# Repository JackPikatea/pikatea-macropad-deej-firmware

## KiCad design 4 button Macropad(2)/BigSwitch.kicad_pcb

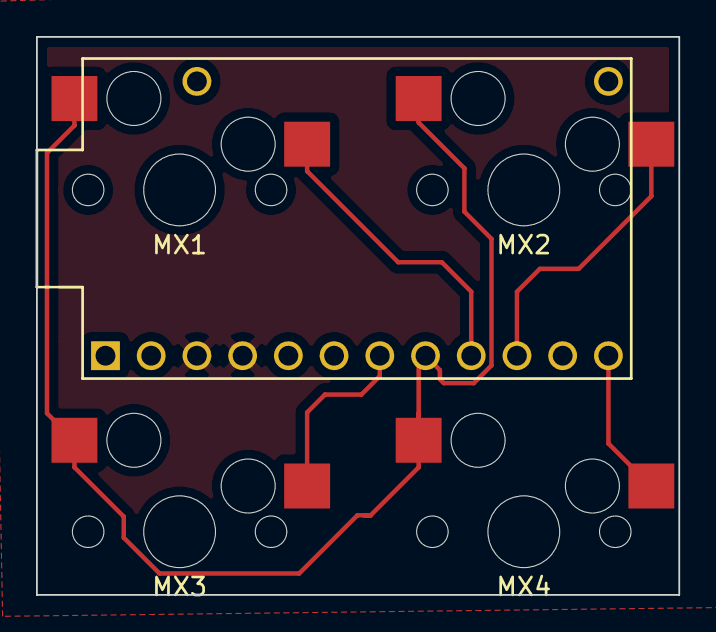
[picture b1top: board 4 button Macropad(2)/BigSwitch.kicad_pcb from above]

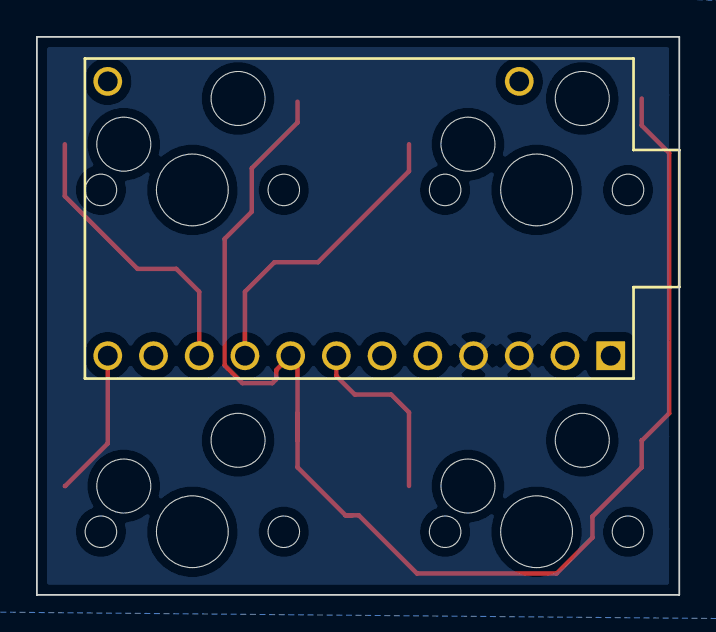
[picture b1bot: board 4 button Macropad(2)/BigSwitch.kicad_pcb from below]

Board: 2 copper layers, 35.7 x 31.0 mm, 5 parts (4 on the bottom side), 6 nets.

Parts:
MX1, MX2, MX3, MX4: MX-NoLED; MXOnly-1U-Hotswap
U1: ProMicro

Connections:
/D4: MX3.1, U1.7
/D5: MX1.2, MX2.2, MX3.2, MX4.2, U1.8
/D6: MX1.1, U1.9
/D7: MX2.1, U1.10
/D9: MX4.1, U1.12
GND: U1.3, U1.4

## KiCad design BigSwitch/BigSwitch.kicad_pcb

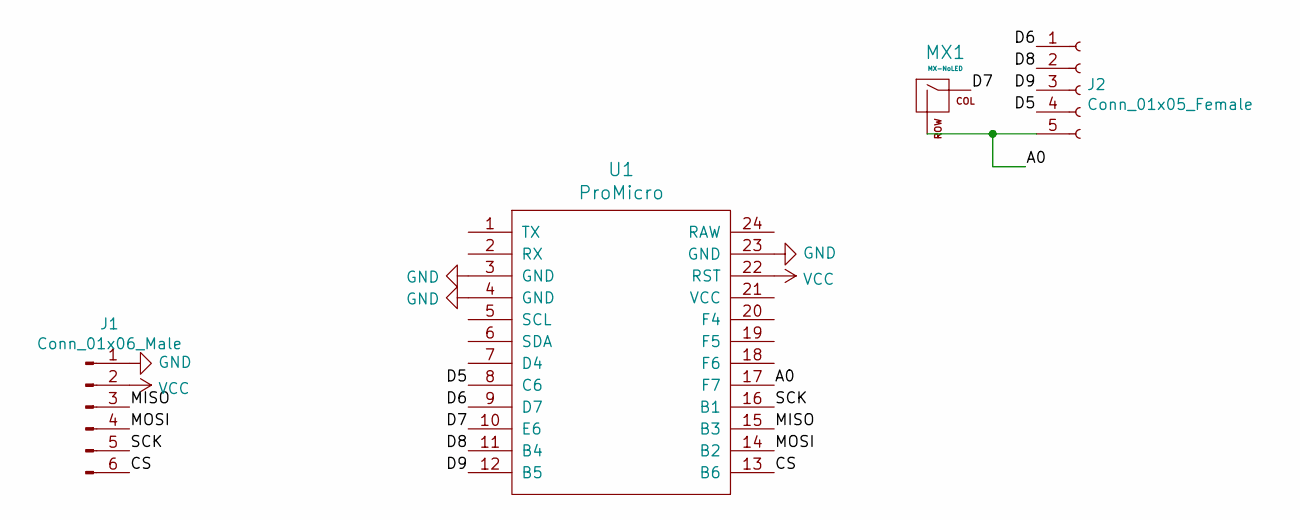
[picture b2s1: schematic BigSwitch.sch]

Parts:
J1: Conn_01x06_Male; SDcardModule-BottomSideDown
J2: Conn_01x05_Female; PinHeader_1x05_P2.54mm_Vertical
MX1: MX-NoLED; BigSwitch
U1: ProMicro

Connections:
/A0: J2.5, MX1.2 (ROW), U1.17 (F7)
/CS: J1.6, U1.13 (B6)
/D5: J2.4, U1.8 (C6)
/D6: J2.1, U1.9 (D7)
/D7: MX1.1 (COL), U1.10 (E6)
/D8: J2.2, U1.11 (B4)
/D9: J2.3, U1.12 (B5)
/MISO: J1.3, U1.15 (B3)
/MOSI: J1.4, U1.14 (B2)
/SCK: J1.5, U1.16 (B1)
GND: J1.1, U1.3 (GND), U1.4 (GND), U1.23 (GND)
VCC: J1.2, U1.22 (RST)

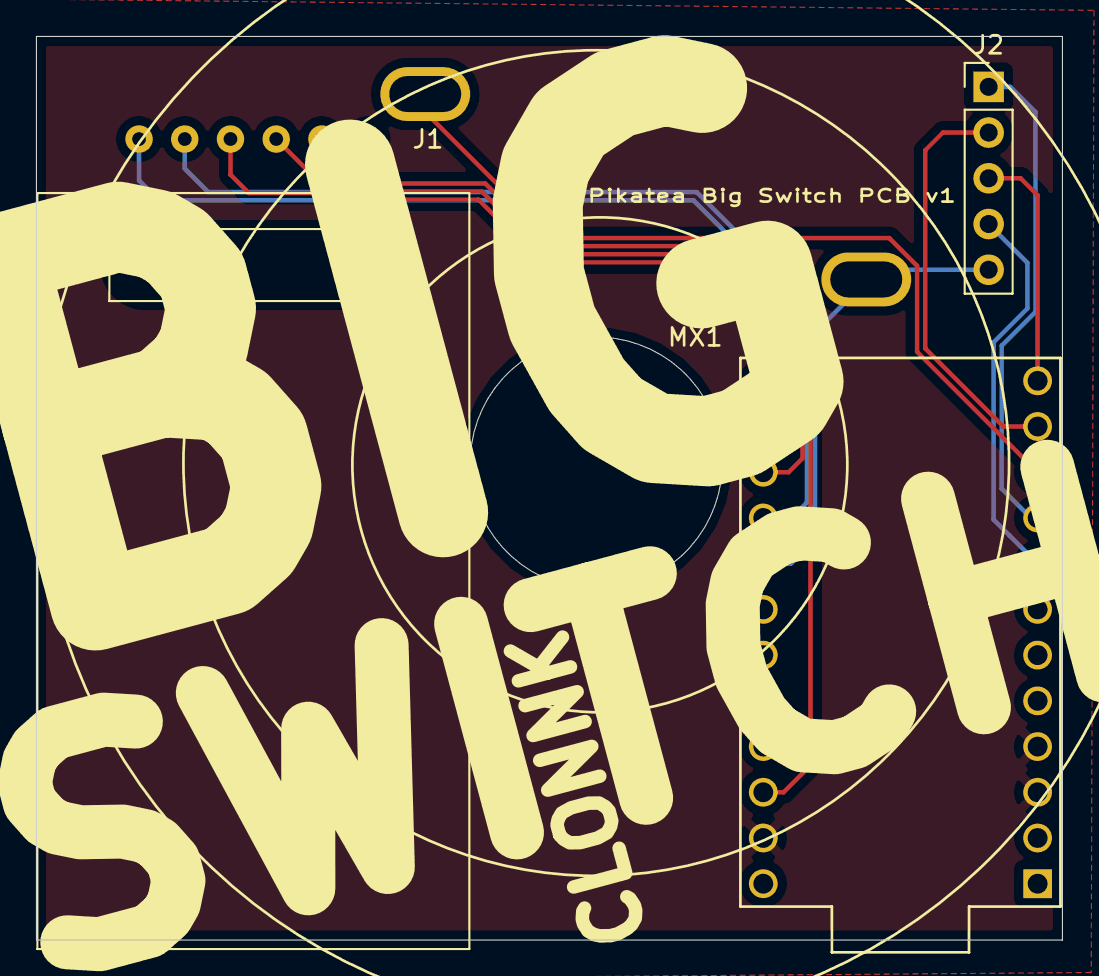
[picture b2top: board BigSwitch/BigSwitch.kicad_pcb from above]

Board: 2 copper layers, 57.0 x 50.2 mm, 4 parts (0 on the bottom side), 12 nets.

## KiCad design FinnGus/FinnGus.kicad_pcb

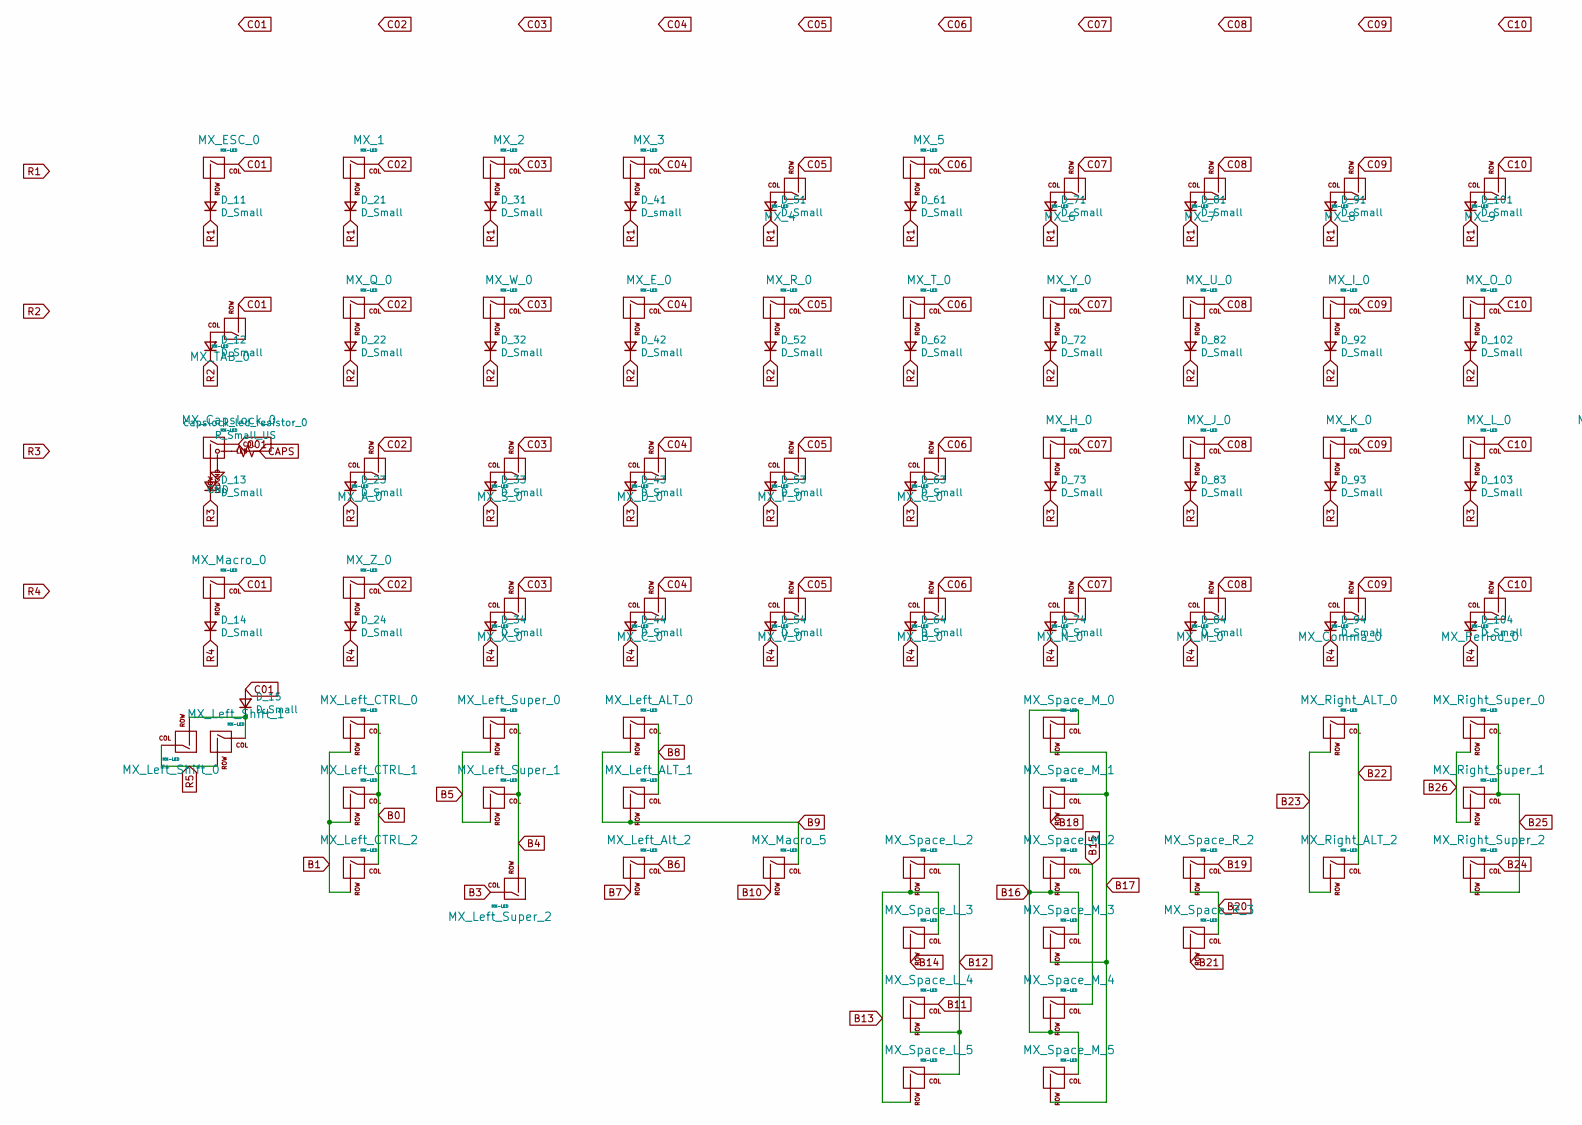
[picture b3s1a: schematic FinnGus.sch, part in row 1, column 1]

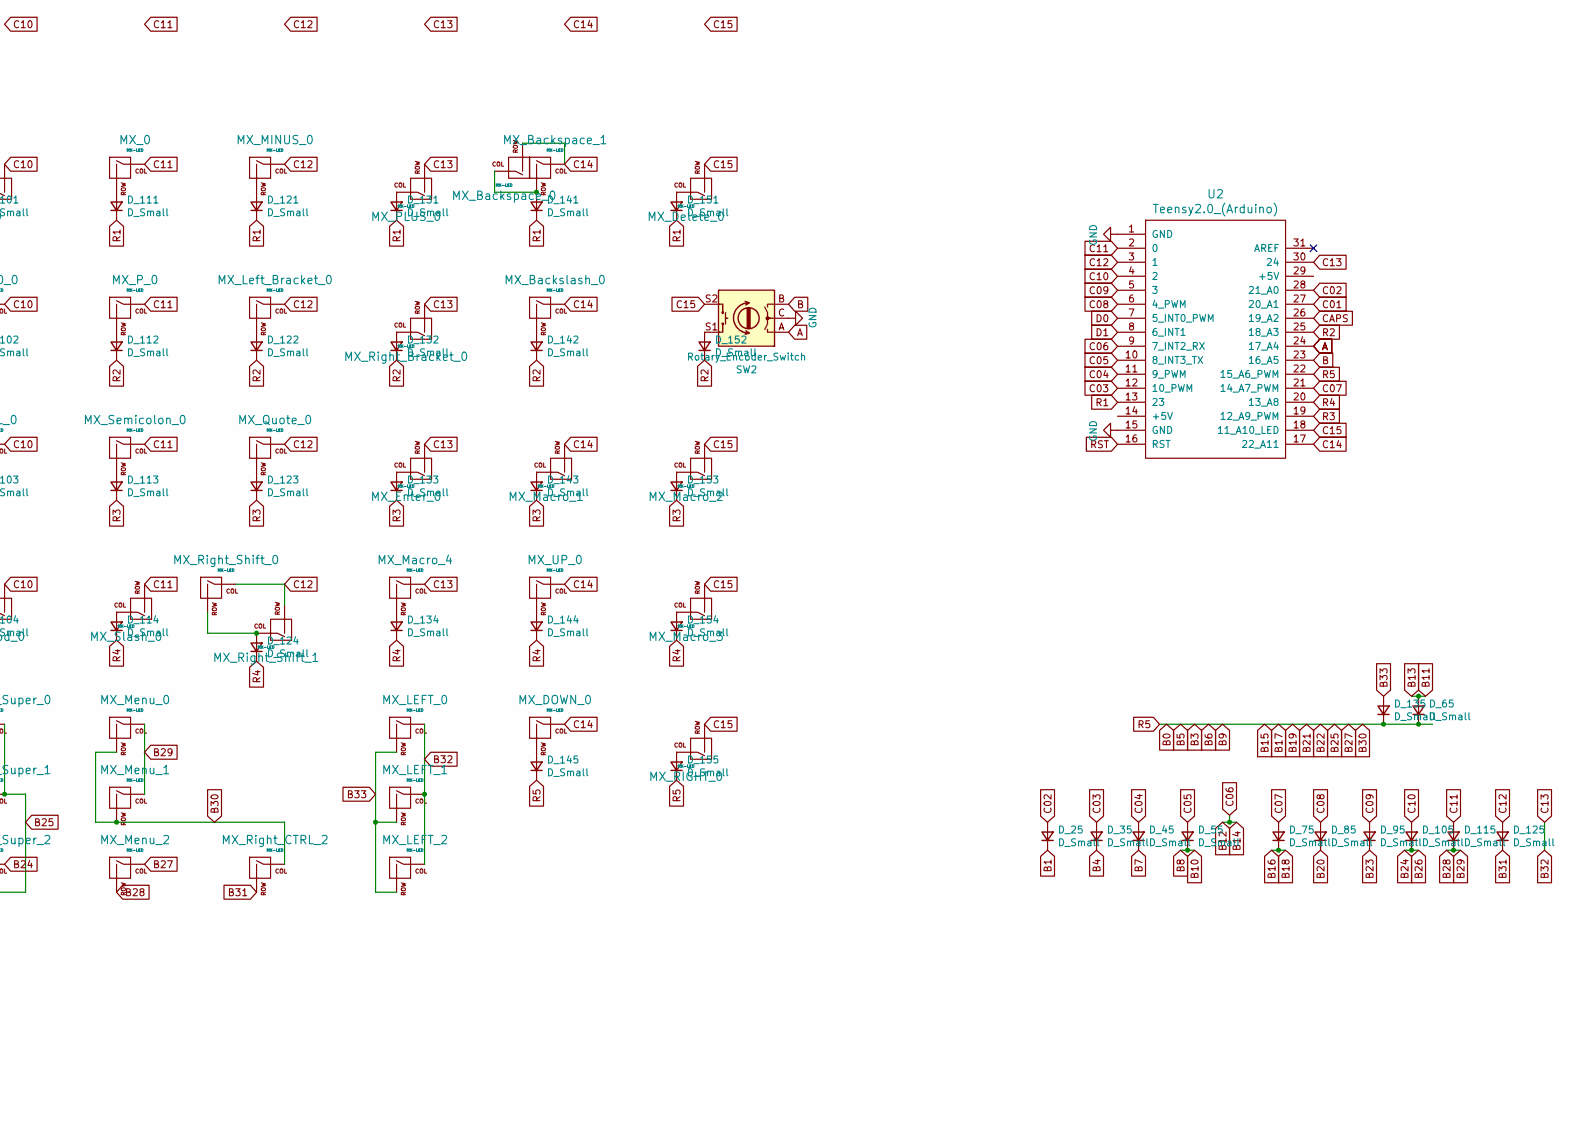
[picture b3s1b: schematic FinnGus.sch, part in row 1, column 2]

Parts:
D_11, D_12, D_13, D_14, D_15, D_21, D_22, D_23, D_24, D_25, D_31, D_32, D_33, D_34, D_35, D_42, D_43, D_44, D_45, D_51, D_52, D_53, D_54, D_55, D_61, D_62, D_63, D_64, D_65, D_71, D_72, D_73, D_74, D_75, D_81, D_82, D_83, D_84, D_85, D_91, D_92, D_93, D_94, D_95, D_101, D_102, D_103, D_104, D_105, D_111, D_112, D_113, D_114, D_115, D_121, D_122, D_123, D_124, D_125, D_131, D_132, D_133, D_134, D_135, D_141, D_142, D_143, D_144, D_145, D_151, D_152, D_153, D_154, D_155: D_Small; D_axial
D_41: D_small; D_axial
MX_0, MX_1, MX_2, MX_3, MX_4, MX_5, MX_6, MX_7, MX_8, MX_9: MX-LED; MXOnly-1U-NoLED
MX_A_0: MX-LED; MXOnly-1U-NoLED
MX_B_0: MX-LED; MXOnly-1U-NoLED
MX_Backslash_0: MX-LED; MXOnly-1.5U-NoLED
MX_Backspace_0: MX-LED; MXOnly-1U-NoLED
MX_Backspace_1: MX-LED; MXOnly-2U-NoLED
MX_C_0: MX-LED; MXOnly-1U-NoLED
MX_Capslock_0: MX-LED; MXOnly-1.75U
MX_Comma_0: MX-LED; MXOnly-1U-NoLED
MX_DOWN_0: MX-LED; MXOnly-1U-NoLED
MX_D_0: MX-LED; MXOnly-1U-NoLED
MX_Delete_0: MX-LED; MXOnly-1U-NoLED
MX_ESC_0: MX-LED; MXOnly-1U-NoLED
MX_E_0: MX-LED; MXOnly-1U-NoLED
MX_Enter_0: MX-LED; MXOnly-2.25U-ReversedStabilizers-NoLED
MX_F_0: MX-LED; MXOnly-1U-NoLED
MX_G_0: MX-LED; MXOnly-1U-NoLED
MX_H_0: MX-LED; MXOnly-1U-NoLED
MX_I_0: MX-LED; MXOnly-1U-NoLED
MX_J_0: MX-LED; MXOnly-1U-NoLED
MX_K_0: MX-LED; MXOnly-1U-NoLED
MX_LEFT_0: MX-LED; MXOnly-1.25U-NoLED
MX_LEFT_1: MX-LED; MXOnly-1.5U-NoLED
MX_LEFT_2: MX-LED; MXOnly-1U-NoLED
MX_L_0: MX-LED; MXOnly-1U-NoLED
MX_Left_ALT_0: MX-LED; MXOnly-1.25U-NoLED
MX_Left_ALT_1: MX-LED; MXOnly-1.5U-NoLED
MX_Left_Alt_2: MX-LED; MXOnly-1U-NoLED
MX_Left_Bracket_0: MX-LED; MXOnly-1U-NoLED
MX_Left_CTRL_0: MX-LED; MXOnly-1.25U-NoLED
MX_Left_CTRL_1: MX-LED; MXOnly-1.5U-NoLED
MX_Left_CTRL_2: MX-LED; MXOnly-1U-NoLED
MX_Left_Shift_0: MX-LED; MXOnly-1.25U-NoLED
MX_Left_Shift_1: MX-LED; MXOnly-2.25U-ReversedStabilizers-NoLED
MX_Left_Super_0: MX-LED; MXOnly-1.25U-NoLED
MX_Left_Super_1, MX_Left_Super_2: MX-LED; MXOnly-1U-NoLED
MX_MINUS_0: MX-LED; MXOnly-1U-NoLED
MX_M_0: MX-LED; MXOnly-1U-NoLED
MX_Macro_0, MX_Macro_1, MX_Macro_2, MX_Macro_3, MX_Macro_4, MX_Macro_5: MX-LED; MXOnly-1U-NoLED
MX_Menu_0: MX-LED; MXOnly-1.25U-NoLED
MX_Menu_1, MX_Menu_2: MX-LED; MXOnly-1U-NoLED
MX_N_0: MX-LED; MXOnly-1U-NoLED
MX_O_0: MX-LED; MXOnly-1U-NoLED
MX_PLUS_0: MX-LED; MXOnly-1U-NoLED
MX_P_0: MX-LED; MXOnly-1U-NoLED
MX_Period_0: MX-LED; MXOnly-1U-NoLED
MX_Q_0: MX-LED; MXOnly-1U-NoLED
MX_Quote_0: MX-LED; MXOnly-1U-NoLED
MX_RIGHT_0: MX-LED; MXOnly-1U-NoLED
MX_R_0: MX-LED; MXOnly-1U-NoLED
MX_Right_ALT_0: MX-LED; MXOnly-1.25U-NoLED
MX_Right_ALT_2: MX-LED; MXOnly-1U-NoLED
MX_Right_Bracket_0: MX-LED; MXOnly-1U-NoLED
MX_Right_CTRL_2: MX-LED; MXOnly-1U-NoLED
MX_Right_Shift_0: MX-LED; MXOnly-2.75U-ReversedStabilizers-NoLED
MX_Right_Shift_1: MX-LED; MXOnly-1.75U-NoLED
MX_Right_Super_0: MX-LED; MXOnly-1.25U-NoLED
MX_Right_Super_1: MX-LED; MXOnly-1.5U-NoLED
MX_Right_Super_2: MX-LED; MXOnly-1U-NoLED
MX_S_0: MX-LED; MXOnly-1U-NoLED
MX_Semicolon_0: MX-LED; MXOnly-1U-NoLED
MX_Slash_0: MX-LED; MXOnly-1U-NoLED
MX_Space_L_2, MX_Space_L_4: MX-LED; MXOnly-2.25U-ReversedStabilizers-NoLED
MX_Space_L_3, MX_Space_L_5: MX-LED; MXOnly-2.75U-ReversedStabilizers-NoLED
MX_Space_M_0: MX-LED; MXOnly-6.25U-ReversedStabilizers-NoLED
MX_Space_M_1: MX-LED; MXOnly-7U-ReversedStabilizers-NoLED
MX_Space_M_2, MX_Space_M_3: MX-LED; MXOnly-1U-NoLED
MX_Space_M_4, MX_Space_M_5: MX-LED; MXOnly-1.25U-NoLED
MX_Space_R_2: MX-LED; MXOnly-2.75U-ReversedStabilizers-NoLED
MX_Space_R_3: MX-LED; MXOnly-2.25U-ReversedStabilizers-NoLED
MX_TAB_0: MX-LED; MXOnly-1.5U-NoLED
MX_T_0: MX-LED; MXOnly-1U-NoLED
MX_UP_0: MX-LED; MXOnly-1U-NoLED
MX_U_0: MX-LED; MXOnly-1U-NoLED
MX_V_0: MX-LED; MXOnly-1U-NoLED
MX_W_0: MX-LED; MXOnly-1U-NoLED
MX_X_0: MX-LED; MXOnly-1U-NoLED
MX_Y_0: MX-LED; MXOnly-1U-NoLED
MX_Z_0: MX-LED; MXOnly-1U-NoLED
SW2: Rotary_Encoder_Switch; Encoder-BI_EN11_HSM0E
U2: Teensy2.0_(Arduino); Teensy2.0
capslock_led_resistor_0: R_Small_US; R_Axial_DIN0204_L3.6mm_D1.6mm_P5.08mm_Horizontal

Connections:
A: SW2.A, U2.24 (17_A4)
B: SW2.B, U2.23 (16_A5)
B0: D_65.1 (K), D_135.1 (K), D_145.1 (K), D_155.1 (K), MX_Left_ALT_0.2 (ROW), MX_Left_ALT_1.2 (ROW), MX_Left_Alt_2.1 (COL), MX_Left_CTRL_0.1 (COL), MX_Left_CTRL_1.1 (COL), MX_Left_CTRL_2.1 (COL), MX_Left_Shift_0.1 (COL), MX_Left_Shift_1.2 (ROW), MX_Left_Super_0.2 (ROW), MX_Left_Super_1.2 (ROW), MX_Left_Super_2.1 (COL), MX_Macro_5.1 (COL), MX_Menu_0.2 (ROW), MX_Menu_1.2 (ROW), MX_Menu_2.1 (COL), MX_Right_ALT_0.1 (COL), MX_Right_ALT_2.1 (COL), MX_Right_CTRL_2.1 (COL), MX_Right_Super_0.1 (COL), MX_Right_Super_1.1 (COL), MX_Right_Super_2.2 (ROW), MX_Space_M_0.2 (ROW), MX_Space_M_1.1 (COL), MX_Space_M_2.1 (COL), MX_Space_M_3.2 (ROW), MX_Space_M_4.1 (COL), MX_Space_M_5.2 (ROW), MX_Space_R_2.1 (COL), MX_Space_R_3.2 (ROW), U2.22 (15_A6_PWM)
B1: D_25.1 (K), MX_Left_CTRL_0.2 (ROW), MX_Left_CTRL_1.2 (ROW), MX_Left_CTRL_2.2 (ROW)
B4: D_35.1 (K), MX_Left_Super_0.1 (COL), MX_Left_Super_1.1 (COL), MX_Left_Super_2.2 (ROW)
B7: D_45.1 (K), MX_Left_Alt_2.2 (ROW)
B10: D_55.1 (K), MX_Left_ALT_0.1 (COL), MX_Left_ALT_1.1 (COL), MX_Macro_5.2 (ROW)
B11: D_65.2 (A), MX_Space_L_2.2 (ROW), MX_Space_L_3.1 (COL), MX_Space_L_4.1 (COL), MX_Space_L_5.2 (ROW)
B12: MX_5.1 (COL), MX_B_0.2 (ROW), MX_G_0.2 (ROW), MX_Space_L_2.1 (COL), MX_Space_L_3.2 (ROW), MX_Space_L_4.2 (ROW), MX_Space_L_5.1 (COL), MX_T_0.1 (COL), U2.9 (7_INT2_RX)
B16: D_75.1 (K), MX_Space_M_0.1 (COL), MX_Space_M_1.2 (ROW), MX_Space_M_2.2 (ROW), MX_Space_M_3.1 (COL), MX_Space_M_4.2 (ROW), MX_Space_M_5.1 (COL)
B20: D_85.1 (K), MX_Space_R_2.2 (ROW), MX_Space_R_3.1 (COL)
B23: D_95.1 (K), MX_Right_ALT_0.2 (ROW), MX_Right_ALT_2.2 (ROW)
B24: D_105.1 (K), MX_Right_Super_0.2 (ROW), MX_Right_Super_1.2 (ROW), MX_Right_Super_2.1 (COL)
B28: D_115.1 (K), MX_Menu_0.1 (COL), MX_Menu_1.1 (COL), MX_Menu_2.2 (ROW)
B31: D_125.1 (K), MX_Right_CTRL_2.2 (ROW)
B32: MX_Enter_0.2 (ROW), MX_LEFT_0.1 (COL), MX_LEFT_1.1 (COL), MX_LEFT_2.1 (COL), MX_Macro_4.1 (COL), MX_PLUS_0.2 (ROW), MX_Right_Bracket_0.2 (ROW), U2.30 (24)
B33: D_135.2 (A), MX_LEFT_0.2 (ROW), MX_LEFT_1.2 (ROW), MX_LEFT_2.2 (ROW)
C01: D_15.2 (A), MX_Capslock_0.1 (COL), MX_ESC_0.1 (COL), MX_Macro_0.1 (COL), MX_TAB_0.2 (ROW), U2.27 (20_A1)
C02: D_25.2 (A), MX_1.1 (COL), MX_A_0.2 (ROW), MX_Q_0.1 (COL), MX_Z_0.1 (COL), U2.28 (21_A0)
C03: D_35.2 (A), MX_2.1 (COL), MX_S_0.2 (ROW), MX_W_0.1 (COL), MX_X_0.2 (ROW), U2.12 (10_PWM)
C04: D_45.2 (A), MX_3.1 (COL), MX_C_0.2 (ROW), MX_D_0.2 (ROW), MX_E_0.1 (COL), U2.11 (9_PWM)
C05: D_55.2 (A), MX_4.2 (ROW), MX_F_0.2 (ROW), MX_R_0.1 (COL), MX_V_0.2 (ROW), U2.10 (8_INT3_TX)
C07: D_75.2 (A), MX_6.2 (ROW), MX_H_0.1 (COL), MX_N_0.2 (ROW), MX_Y_0.1 (COL), U2.21 (14_A7_PWM)
C08: D_85.2 (A), MX_7.2 (ROW), MX_J_0.1 (COL), MX_M_0.2 (ROW), MX_U_0.1 (COL), U2.6 (4_PWM)
C09: D_95.2 (A), MX_8.2 (ROW), MX_Comma_0.2 (ROW), MX_I_0.1 (COL), MX_K_0.1 (COL), U2.5 (3)
C10: D_105.2 (A), MX_9.2 (ROW), MX_L_0.1 (COL), MX_O_0.1 (COL), MX_Period_0.2 (ROW), U2.4 (2)
C11: D_115.2 (A), MX_0.1 (COL), MX_P_0.1 (COL), MX_Semicolon_0.1 (COL), MX_Slash_0.2 (ROW), U2.2 (0)
C12: D_125.2 (A), MX_Left_Bracket_0.1 (COL), MX_MINUS_0.1 (COL), MX_Quote_0.1 (COL), MX_Right_Shift_0.1 (COL), MX_Right_Shift_1.2 (ROW), U2.3 (1)
C14: MX_Backslash_0.1 (COL), MX_Backspace_0.2 (ROW), MX_Backspace_1.1 (COL), MX_DOWN_0.1 (COL), MX_Macro_1.2 (ROW), MX_UP_0.1 (COL), U2.17 (22_A11)
C15: MX_Delete_0.2 (ROW), MX_Macro_2.2 (ROW), MX_Macro_3.2 (ROW), MX_RIGHT_0.2 (ROW), SW2.S2, U2.18 (11_A10_LED)
CAPS: U2.26 (19_A2), capslock_led_resistor_0.2
D0: U2.7 (5_INT0_PWM)
D1: U2.8 (6_INT1)
GND: MX_Capslock_0.4 (LEDGND), SW2.C, U2.1 (GND), U2.15 (GND)
unnamed: D_11.2 (A), MX_ESC_0.2 (ROW)
unnamed: D_12.2 (A), MX_TAB_0.1 (COL)
unnamed: D_13.2 (A), MX_Capslock_0.2 (ROW)
unnamed: D_14.2 (A), MX_Macro_0.2 (ROW)
unnamed: D_15.1 (K), MX_Left_Shift_0.2 (ROW), MX_Left_Shift_1.1 (COL)
unnamed: D_21.2 (A), MX_1.2 (ROW)
unnamed: D_22.2 (A), MX_Q_0.2 (ROW)
unnamed: D_23.2 (A), MX_A_0.1 (COL)
unnamed: D_24.2 (A), MX_Z_0.2 (ROW)
unnamed: D_31.2 (A), MX_2.2 (ROW)
unnamed: D_32.2 (A), MX_W_0.2 (ROW)
unnamed: D_33.2 (A), MX_S_0.1 (COL)
unnamed: D_34.2 (A), MX_X_0.1 (COL)
unnamed: D_41.2 (A), MX_3.2 (ROW)
unnamed: D_42.2 (A), MX_E_0.2 (ROW)
unnamed: D_43.2 (A), MX_D_0.1 (COL)
unnamed: D_44.2 (A), MX_C_0.1 (COL)
unnamed: D_51.2 (A), MX_4.1 (COL)
unnamed: D_52.2 (A), MX_R_0.2 (ROW)
unnamed: D_53.2 (A), MX_F_0.1 (COL)
unnamed: D_54.2 (A), MX_V_0.1 (COL)
unnamed: D_61.2 (A), MX_5.2 (ROW)
unnamed: D_62.2 (A), MX_T_0.2 (ROW)
unnamed: D_63.2 (A), MX_G_0.1 (COL)
unnamed: D_64.2 (A), MX_B_0.1 (COL)
unnamed: D_71.2 (A), MX_6.1 (COL)
unnamed: D_72.2 (A), MX_Y_0.2 (ROW)
unnamed: D_73.2 (A), MX_H_0.2 (ROW)
unnamed: D_74.2 (A), MX_N_0.1 (COL)
unnamed: D_81.2 (A), MX_7.1 (COL)
unnamed: D_82.2 (A), MX_U_0.2 (ROW)
unnamed: D_83.2 (A), MX_J_0.2 (ROW)
unnamed: D_84.2 (A), MX_M_0.1 (COL)
unnamed: D_91.2 (A), MX_8.1 (COL)
unnamed: D_92.2 (A), MX_I_0.2 (ROW)
unnamed: D_93.2 (A), MX_K_0.2 (ROW)
unnamed: D_94.2 (A), MX_Comma_0.1 (COL)
unnamed: D_101.2 (A), MX_9.1 (COL)
unnamed: D_102.2 (A), MX_O_0.2 (ROW)
unnamed: D_103.2 (A), MX_L_0.2 (ROW)
unnamed: D_104.2 (A), MX_Period_0.1 (COL)
unnamed: D_111.2 (A), MX_0.2 (ROW)
unnamed: D_112.2 (A), MX_P_0.2 (ROW)
unnamed: D_113.2 (A), MX_Semicolon_0.2 (ROW)
unnamed: D_114.2 (A), MX_Slash_0.1 (COL)
unnamed: D_121.2 (A), MX_MINUS_0.2 (ROW)
unnamed: D_122.2 (A), MX_Left_Bracket_0.2 (ROW)
unnamed: D_123.2 (A), MX_Quote_0.2 (ROW)
unnamed: D_124.2 (A), MX_Right_Shift_0.2 (ROW), MX_Right_Shift_1.1 (COL)
unnamed: D_131.2 (A), MX_PLUS_0.1 (COL)
unnamed: D_132.2 (A), MX_Right_Bracket_0.1 (COL)
unnamed: D_133.2 (A), MX_Enter_0.1 (COL)
unnamed: D_134.2 (A), MX_Macro_4.2 (ROW)
unnamed: D_141.2 (A), MX_Backspace_0.1 (COL), MX_Backspace_1.2 (ROW)
unnamed: D_142.2 (A), MX_Backslash_0.2 (ROW)
unnamed: D_143.2 (A), MX_Macro_1.1 (COL)
unnamed: D_144.2 (A), MX_UP_0.2 (ROW)
unnamed: D_145.2 (A), MX_DOWN_0.2 (ROW)
unnamed: D_151.2 (A), MX_Delete_0.1 (COL)
unnamed: D_152.2 (A), SW2.S1
unnamed: D_153.2 (A), MX_Macro_2.1 (COL)
unnamed: D_154.2 (A), MX_Macro_3.1 (COL)
unnamed: D_155.2 (A), MX_RIGHT_0.1 (COL)
unnamed: MX_Capslock_0.3 (LED), capslock_led_resistor_0.1
R1: D_11.1 (K), D_21.1 (K), D_31.1 (K), D_41.1 (K), D_51.1 (K), D_61.1 (K), D_71.1 (K), D_81.1 (K), D_91.1 (K), D_101.1 (K), D_111.1 (K), D_121.1 (K), D_131.1 (K), D_141.1 (K), D_151.1 (K), U2.13 (23)
R2: D_12.1 (K), D_22.1 (K), D_32.1 (K), D_42.1 (K), D_52.1 (K), D_62.1 (K), D_72.1 (K), D_82.1 (K), D_92.1 (K), D_102.1 (K), D_112.1 (K), D_122.1 (K), D_132.1 (K), D_142.1 (K), D_152.1 (K), U2.25 (18_A3)
R3: D_13.1 (K), D_23.1 (K), D_33.1 (K), D_43.1 (K), D_53.1 (K), D_63.1 (K), D_73.1 (K), D_83.1 (K), D_93.1 (K), D_103.1 (K), D_113.1 (K), D_123.1 (K), D_133.1 (K), D_143.1 (K), D_153.1 (K), U2.19 (12_A9_PWM)
R4: D_14.1 (K), D_24.1 (K), D_34.1 (K), D_44.1 (K), D_54.1 (K), D_64.1 (K), D_74.1 (K), D_84.1 (K), D_94.1 (K), D_104.1 (K), D_114.1 (K), D_124.1 (K), D_134.1 (K), D_144.1 (K), D_154.1 (K), U2.20 (13_A8)
RST: U2.16 (RST)

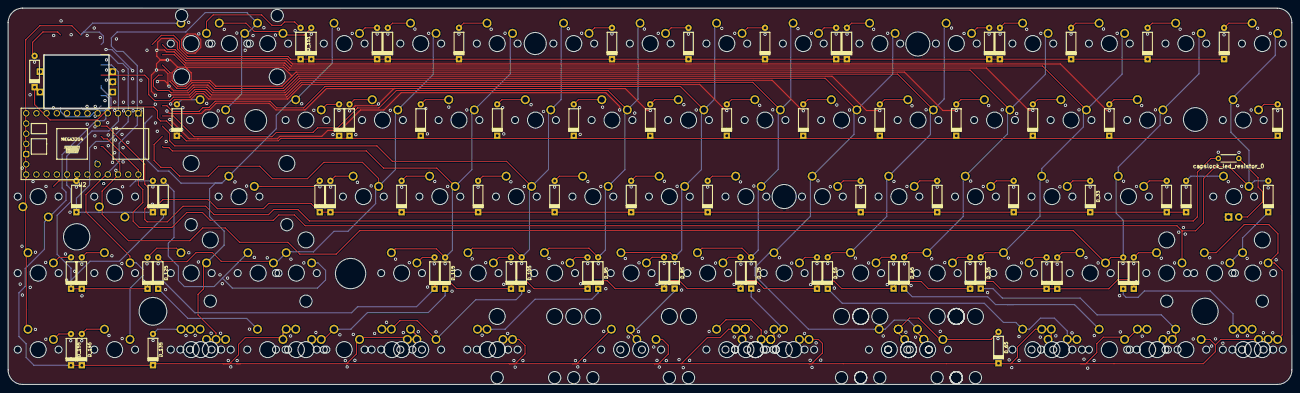
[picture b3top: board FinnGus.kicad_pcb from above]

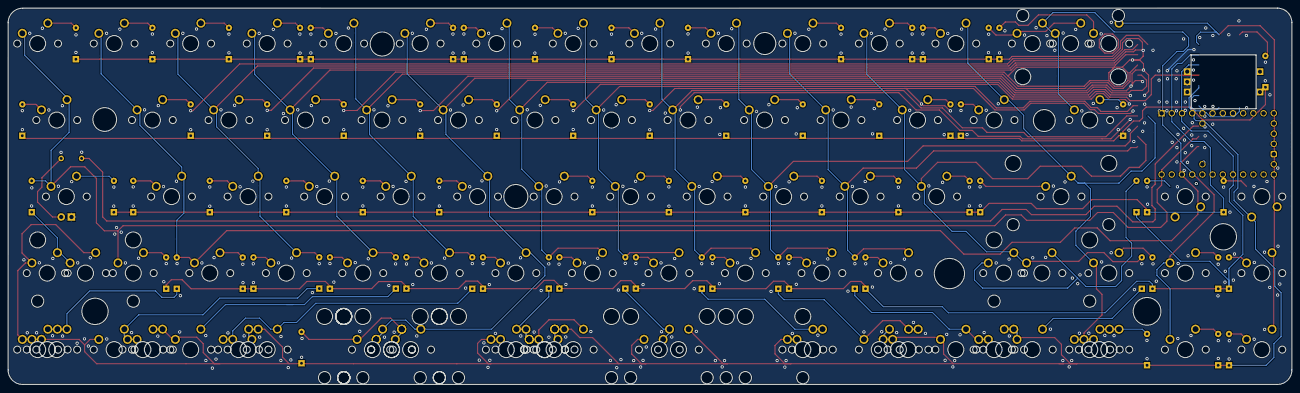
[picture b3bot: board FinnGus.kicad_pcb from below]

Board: 2 copper layers, 319.6 x 93.7 mm, 177 parts (99 on the bottom side), 100 nets.

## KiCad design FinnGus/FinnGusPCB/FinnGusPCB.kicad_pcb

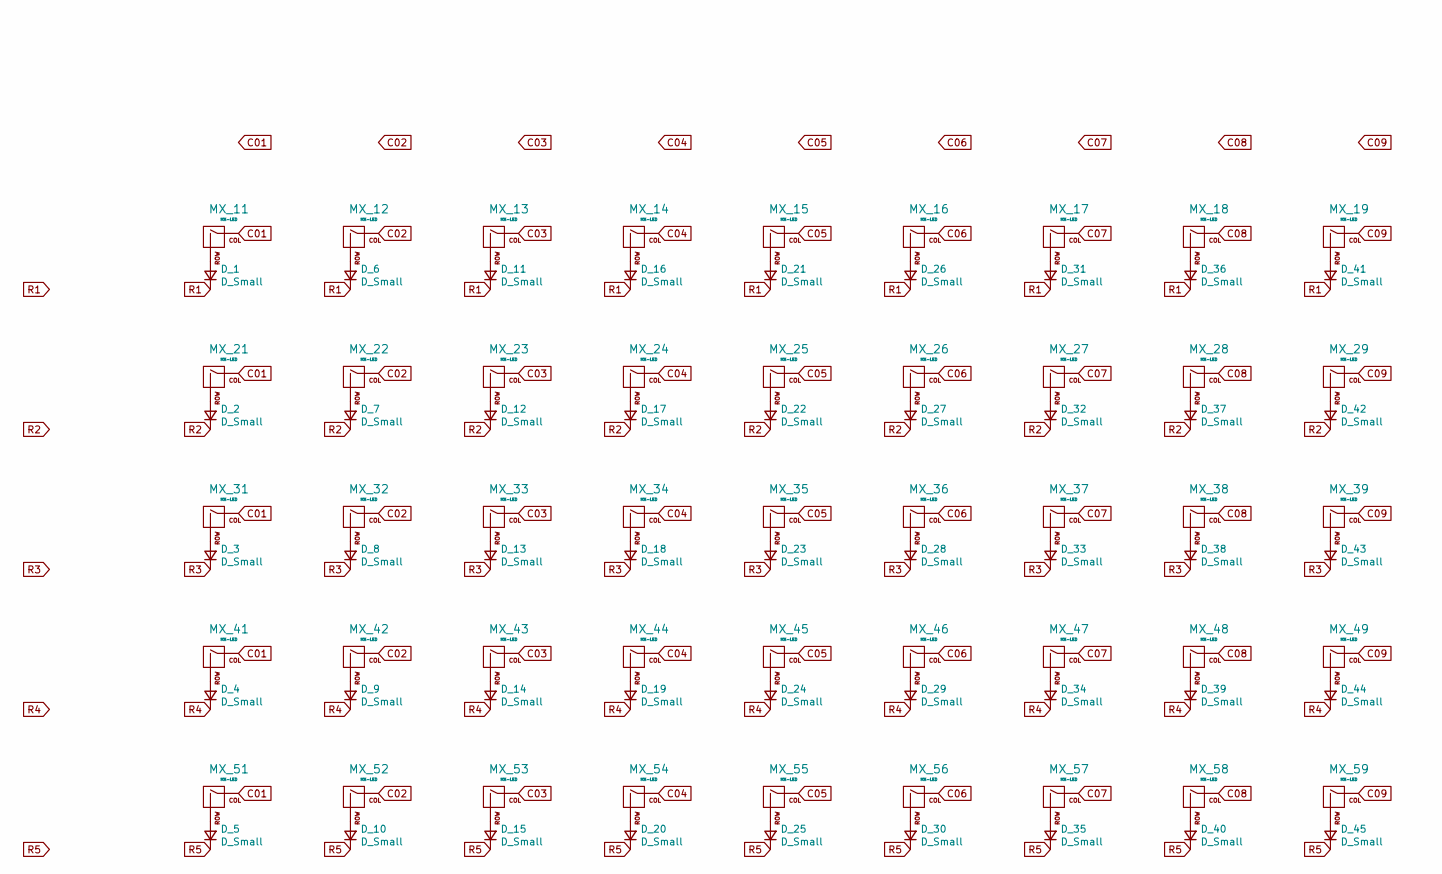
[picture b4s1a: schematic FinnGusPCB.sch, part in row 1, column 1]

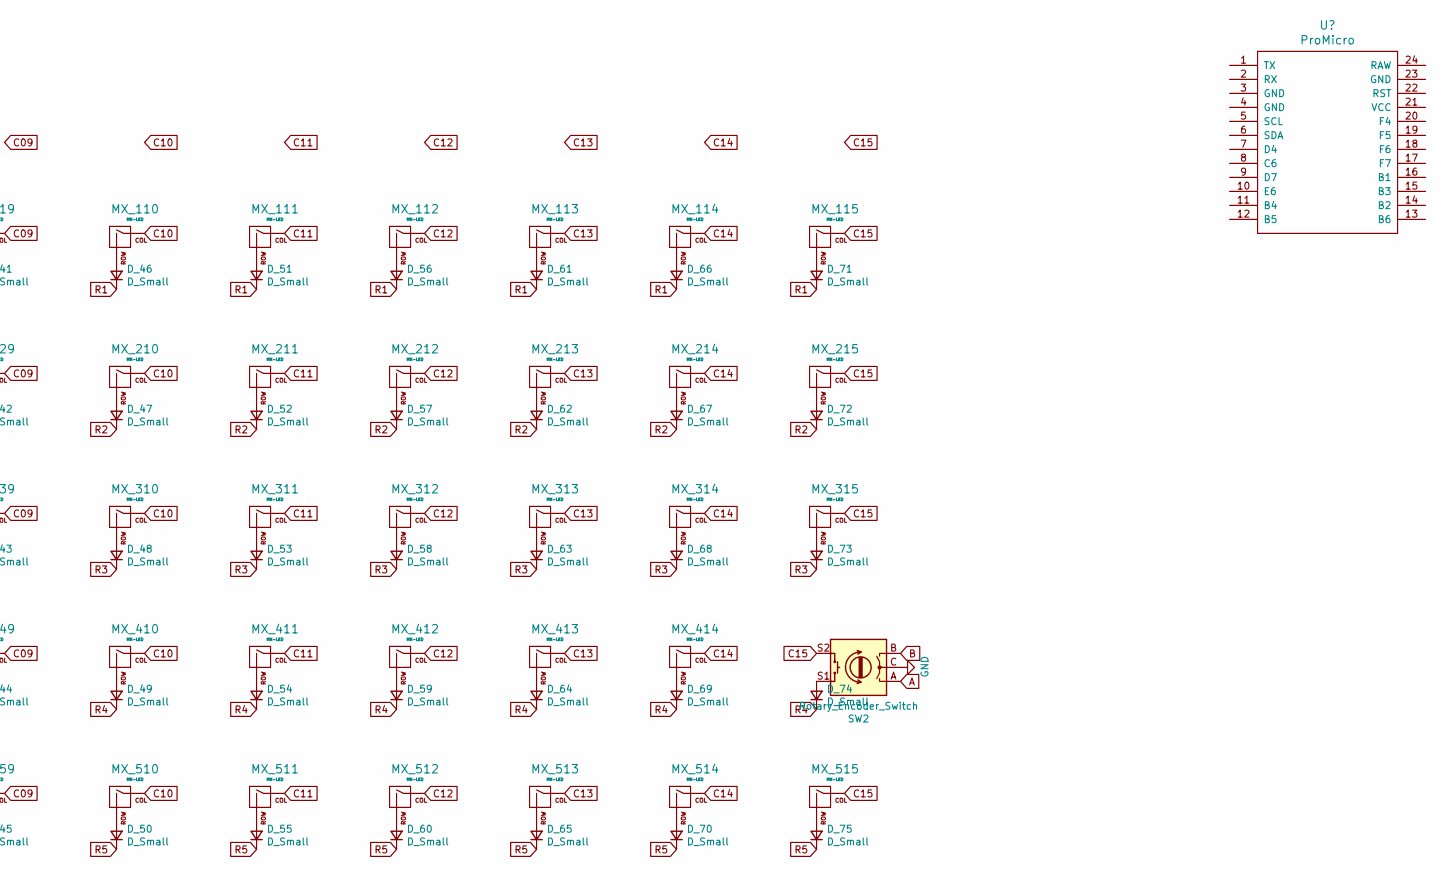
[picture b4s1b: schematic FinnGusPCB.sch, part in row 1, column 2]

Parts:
D_1, D_2, D_3, D_4, D_5, D_6, D_7, D_8, D_9, D_10, D_11, D_12, D_13, D_14, D_15, D_16, D_17, D_18, D_19, D_20, D_21, D_22, D_23, D_24, D_25, D_26, D_27, D_28, D_29, D_30, D_31, D_32, D_33, D_34, D_35, D_36, D_37, D_38, D_39, D_40, D_41, D_42, D_43, D_44, D_45, D_46, D_47, D_48, D_49, D_50, D_51, D_52, D_53, D_54, D_55, D_56, D_57, D_58, D_59, D_60, D_61, D_62, D_63, D_64, D_65, D_66, D_67, D_68, D_69, D_70, D_71, D_72, D_73, D_74, D_75: D_Small; D_axial
MX_11, MX_12, MX_13, MX_14, MX_15, MX_16, MX_17, MX_18, MX_19, MX_21, MX_22, MX_23, MX_24, MX_25, MX_26, MX_27, MX_28, MX_29, MX_31, MX_32, MX_33, MX_34, MX_35, MX_36, MX_37, MX_38, MX_39, MX_41, MX_42, MX_43, MX_44, MX_45, MX_46, MX_47, MX_48, MX_49, MX_51, MX_52, MX_53, MX_54, MX_55, MX_56, MX_57, MX_58, MX_59, MX_110, MX_111, MX_112, MX_113, MX_114, MX_115, MX_210, MX_211, MX_212, MX_213, MX_214, MX_215, MX_310, MX_311, MX_312, MX_313, MX_314, MX_315, MX_410, MX_411, MX_412, MX_413, MX_414, MX_510, MX_511, MX_512, MX_513, MX_514, MX_515: MX-LED; MXOnly-1U-NoLED
SW2: Rotary_Encoder_Switch; Encoder-BI_EN11_HSM0E

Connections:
A: SW2.A; also elsewhere on the board
B: SW2.B; also elsewhere on the board
C01: MX_11.1 (COL), MX_21.1 (COL), MX_31.1 (COL), MX_41.1 (COL), MX_51.1 (COL); also elsewhere on the board
C02: MX_12.1 (COL), MX_22.1 (COL), MX_32.1 (COL), MX_42.1 (COL), MX_52.1 (COL); also elsewhere on the board
C03: MX_13.1 (COL), MX_23.1 (COL), MX_33.1 (COL), MX_43.1 (COL), MX_53.1 (COL); also elsewhere on the board
C04: MX_14.1 (COL), MX_24.1 (COL), MX_34.1 (COL), MX_44.1 (COL), MX_54.1 (COL); also elsewhere on the board
C05: MX_15.1 (COL), MX_25.1 (COL), MX_35.1 (COL), MX_45.1 (COL), MX_55.1 (COL); also elsewhere on the board
C06: MX_16.1 (COL), MX_26.1 (COL), MX_36.1 (COL), MX_46.1 (COL), MX_56.1 (COL); also elsewhere on the board
C07: MX_17.1 (COL), MX_27.1 (COL), MX_37.1 (COL), MX_47.1 (COL), MX_57.1 (COL); also elsewhere on the board
C08: MX_18.1 (COL), MX_28.1 (COL), MX_38.1 (COL), MX_48.1 (COL), MX_58.1 (COL); also elsewhere on the board
C09: MX_19.1 (COL), MX_29.1 (COL), MX_39.1 (COL), MX_49.1 (COL), MX_59.1 (COL); also elsewhere on the board
C10: MX_110.1 (COL), MX_210.1 (COL), MX_310.1 (COL), MX_410.1 (COL), MX_510.1 (COL); also elsewhere on the board
C11: MX_111.1 (COL), MX_211.1 (COL), MX_311.1 (COL), MX_411.1 (COL), MX_511.1 (COL); also elsewhere on the board
C12: MX_112.1 (COL), MX_212.1 (COL), MX_312.1 (COL), MX_412.1 (COL), MX_512.1 (COL); also elsewhere on the board
C13: MX_113.1 (COL), MX_213.1 (COL), MX_313.1 (COL), MX_413.1 (COL), MX_513.1 (COL); also elsewhere on the board
C14: MX_114.1 (COL), MX_214.1 (COL), MX_314.1 (COL), MX_414.1 (COL), MX_514.1 (COL); also elsewhere on the board
GND: SW2.C; also elsewhere on the board
unnamed: D_1.2 (A), MX_11.2 (ROW)
unnamed: D_2.2 (A), MX_21.2 (ROW)
unnamed: D_3.2 (A), MX_31.2 (ROW)
unnamed: D_4.2 (A), MX_41.2 (ROW)
unnamed: D_5.2 (A), MX_51.2 (ROW)
unnamed: D_6.2 (A), MX_12.2 (ROW)
unnamed: D_7.2 (A), MX_22.2 (ROW)
unnamed: D_8.2 (A), MX_32.2 (ROW)
unnamed: D_9.2 (A), MX_42.2 (ROW)
unnamed: D_10.2 (A), MX_52.2 (ROW)
unnamed: D_11.2 (A), MX_13.2 (ROW)
unnamed: D_12.2 (A), MX_23.2 (ROW)
unnamed: D_13.2 (A), MX_33.2 (ROW)
unnamed: D_14.2 (A), MX_43.2 (ROW)
unnamed: D_15.2 (A), MX_53.2 (ROW)
unnamed: D_16.2 (A), MX_14.2 (ROW)
unnamed: D_17.2 (A), MX_24.2 (ROW)
unnamed: D_18.2 (A), MX_34.2 (ROW)
unnamed: D_19.2 (A), MX_44.2 (ROW)
unnamed: D_20.2 (A), MX_54.2 (ROW)
unnamed: D_21.2 (A), MX_15.2 (ROW)
unnamed: D_22.2 (A), MX_25.2 (ROW)
unnamed: D_23.2 (A), MX_35.2 (ROW)
unnamed: D_24.2 (A), MX_45.2 (ROW)
unnamed: D_25.2 (A), MX_55.2 (ROW)
unnamed: D_26.2 (A), MX_16.2 (ROW)
unnamed: D_27.2 (A), MX_26.2 (ROW)
unnamed: D_28.2 (A), MX_36.2 (ROW)
unnamed: D_29.2 (A), MX_46.2 (ROW)
unnamed: D_30.2 (A), MX_56.2 (ROW)
unnamed: D_31.2 (A), MX_17.2 (ROW)
unnamed: D_32.2 (A), MX_27.2 (ROW)
unnamed: D_33.2 (A), MX_37.2 (ROW)
unnamed: D_34.2 (A), MX_47.2 (ROW)
unnamed: D_35.2 (A), MX_57.2 (ROW)
unnamed: D_36.2 (A), MX_18.2 (ROW)
unnamed: D_37.2 (A), MX_28.2 (ROW)
unnamed: D_38.2 (A), MX_38.2 (ROW)
unnamed: D_39.2 (A), MX_48.2 (ROW)
unnamed: D_40.2 (A), MX_58.2 (ROW)
unnamed: D_41.2 (A), MX_19.2 (ROW)
unnamed: D_42.2 (A), MX_29.2 (ROW)
unnamed: D_43.2 (A), MX_39.2 (ROW)
unnamed: D_44.2 (A), MX_49.2 (ROW)
unnamed: D_45.2 (A), MX_59.2 (ROW)
unnamed: D_46.2 (A), MX_110.2 (ROW)
unnamed: D_47.2 (A), MX_210.2 (ROW)
unnamed: D_48.2 (A), MX_310.2 (ROW)
unnamed: D_49.2 (A), MX_410.2 (ROW)
unnamed: D_50.2 (A), MX_510.2 (ROW)
unnamed: D_51.2 (A), MX_111.2 (ROW)
unnamed: D_52.2 (A), MX_211.2 (ROW)
unnamed: D_53.2 (A), MX_311.2 (ROW)
unnamed: D_54.2 (A), MX_411.2 (ROW)
unnamed: D_55.2 (A), MX_511.2 (ROW)
unnamed: D_56.2 (A), MX_112.2 (ROW)
unnamed: D_57.2 (A), MX_212.2 (ROW)
unnamed: D_58.2 (A), MX_312.2 (ROW)
unnamed: D_59.2 (A), MX_412.2 (ROW)
unnamed: D_60.2 (A), MX_512.2 (ROW)
unnamed: D_61.2 (A), MX_113.2 (ROW)
unnamed: D_62.2 (A), MX_213.2 (ROW)
unnamed: D_63.2 (A), MX_313.2 (ROW)
unnamed: D_64.2 (A), MX_413.2 (ROW)
unnamed: D_65.2 (A), MX_513.2 (ROW)
unnamed: D_66.2 (A), MX_114.2 (ROW)
unnamed: D_67.2 (A), MX_214.2 (ROW)
unnamed: D_68.2 (A), MX_314.2 (ROW)
unnamed: D_69.2 (A), MX_414.2 (ROW)
unnamed: D_70.2 (A), MX_514.2 (ROW)
unnamed: D_71.2 (A), MX_115.2 (ROW)
unnamed: D_72.2 (A), MX_215.2 (ROW)
unnamed: D_73.2 (A), MX_315.2 (ROW)
unnamed: D_75.2 (A), MX_515.2 (ROW)
R1: D_1.1 (K), D_6.1 (K), D_11.1 (K), D_16.1 (K), D_21.1 (K), D_26.1 (K), D_31.1 (K), D_36.1 (K), D_41.1 (K), D_46.1 (K), D_51.1 (K), D_56.1 (K), D_61.1 (K), D_66.1 (K), D_71.1 (K); also elsewhere on the board
R2: D_2.1 (K), D_7.1 (K), D_12.1 (K), D_17.1 (K), D_22.1 (K), D_27.1 (K), D_32.1 (K), D_37.1 (K), D_42.1 (K), D_47.1 (K), D_52.1 (K), D_57.1 (K), D_62.1 (K), D_67.1 (K), D_72.1 (K); also elsewhere on the board
R3: D_3.1 (K), D_8.1 (K), D_13.1 (K), D_18.1 (K), D_23.1 (K), D_28.1 (K), D_33.1 (K), D_38.1 (K), D_43.1 (K), D_48.1 (K), D_53.1 (K), D_58.1 (K), D_63.1 (K), D_68.1 (K), D_73.1 (K); also elsewhere on the board
R4: D_4.1 (K), D_9.1 (K), D_14.1 (K), D_19.1 (K), D_24.1 (K), D_29.1 (K), D_34.1 (K), D_39.1 (K), D_44.1 (K), D_49.1 (K), D_54.1 (K), D_59.1 (K), D_64.1 (K), D_69.1 (K), D_74.1 (K); also elsewhere on the board
R5: D_5.1 (K), D_10.1 (K), D_15.1 (K), D_20.1 (K), D_25.1 (K), D_30.1 (K), D_35.1 (K), D_40.1 (K), D_45.1 (K), D_50.1 (K), D_55.1 (K), D_60.1 (K), D_65.1 (K), D_70.1 (K), D_75.1 (K); also elsewhere on the board

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
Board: 2 copper layers, 152 parts (71 on the bottom side), 98 nets, no tracks yet.

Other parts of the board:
D_152: D_Small; D_axial
U2: Teensy2.0_(Arduino); Teensy2.0

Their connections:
A: U2.24; also elsewhere on the board
B: U2.23; also elsewhere on the board
C01: U2.27; also elsewhere on the board
C02: U2.28; also elsewhere on the board
C03: U2.12; also elsewhere on the board
C04: U2.11; also elsewhere on the board
C05: U2.10; also elsewhere on the board
C06: U2.9; also elsewhere on the board
C07: U2.21; also elsewhere on the board
C08: U2.6; also elsewhere on the board
C09: U2.5; also elsewhere on the board
C10: U2.4; also elsewhere on the board
C11: U2.2; also elsewhere on the board
C12: U2.3; also elsewhere on the board
C13: U2.30; also elsewhere on the board
C14: U2.17; also elsewhere on the board
GND: U2.1, U2.15; also elsewhere on the board
R1: U2.13; also elsewhere on the board
R2: U2.25; also elsewhere on the board
R3: U2.19; also elsewhere on the board
R4: U2.20; also elsewhere on the board
R5: U2.22; also elsewhere on the board

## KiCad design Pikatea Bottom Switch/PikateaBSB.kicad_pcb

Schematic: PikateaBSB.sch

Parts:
C1, C2, C4: 100nF; C_0805_2012Metric
C3: 10uF; C_0805_2012Metric
J1: Conn_01x16; PinHeader_1x16_P2.54mm_Vertical
J2, J3: Conn_01x03; PinHeader_1x03_P2.54mm_Vertical
MX1, MX2, MX3, MX4, MX5: MX-NoLED; MX-1U
R1, R2, R3, R4: 3.3K; R_0805_2012Metric
SW1: Rotary_Encoder_Switch; RotaryEncoder_Alps_EC12E-Switch_Vertical_H20mm
SW2: SW_DPST; SW_SPST_TL3342
U1: AMS1117-3.3; SOT-223-3_TabPin2
U2: 74LVC125APW,118; TSSOP-14-1EP_4.4x5mm_P0.65mm
XS1: SD_ebay-uSD-push_push_SMD; Conn_uSDcard

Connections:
/3.3V: C1.1, C3.1, C4.1, U1.2 (VO), U2.14 (VCC), XS1.4
/5v: C2.1, J1.1, U1.3 (VI)
/A0: J1.3, J3.3, MX1.2 (ROW), MX2.2 (ROW), MX3.2 (ROW), MX4.2 (ROW), MX5.2 (ROW), SW1.S2
/CS: J1.5, R2.1
/D2: J1.12, J3.1, SW1.S1
/D3: J1.13, J2.1, SW1.B
/D4: J1.9, J2.3, SW1.A
/D5: J1.4, MX3.1 (COL)
/D6: J1.8, MX2.1 (COL)
/D7: J1.2, MX5.1 (COL)
/D8: J1.7, MX4.1 (COL)
/D9: J1.6, MX1.1 (COL)
/MISO: J1.14, U2.11 (4Y)
/MOSI: J1.11, R3.1
/RESET: J1.16, SW2.2
/SCK: J1.10, R4.1
GND: C1.2, C2.2, C3.2, C4.2, J1.15, J2.2, SW1.C, SW2.1, U1.1 (GND), U2.1 (1~OE), U2.4 (2~OE), U2.7 (GND), U2.10 (3~OE), U2.13 (4~OE), XS1.6
unnamed: R1.1, U2.12 (4A)
unnamed: R1.2, XS1.7
unnamed: R2.2, U2.9 (3A)
unnamed: R3.2, U2.2 (1A)
unnamed: R4.2, U2.5 (2A)
unnamed: U2.3 (1Y), XS1.3
unnamed: U2.6 (2Y), XS1.5
unnamed: U2.8 (3Y), XS1.2
